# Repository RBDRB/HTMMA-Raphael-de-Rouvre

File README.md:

# HTMMA-Raphael-de-Rouvre
## Traqueur GPS Hors-ligne
Le PCB est destiné à construire un GPS de randonnée hors ligne.
L'objectif n'est pas de reproduire une smartwatch ou un GPS de navigation complet, mais de faire un petit appareil simple et autonome (sauf affichage externe en wifi sur l'ESP) pour l'exécution d'une trace GPX et le suivi d'une trace GPX.

### Choix des composants 

- Calculateur : Pour faire fonctionner les composants entre eux, traiter le GPX et l'interface graphique, et la transmettre en wifi
-> XIAO ESP 32 S3 : Celui à disposition, mais qui s'est avéré parfait pour le projet avec sa taille réduite et ses nombreux GPIO
  
- GPS : Pour récuperer la position en temps réel de l'appareil
-> ATGM336H : Module GNSS peu coûteux, compact, faible consommation par rapport à de nombreuses solutions GNSS plus complexes, sortie UART simple
  
- Mesure d'altitude
-> BMP280 : Très petit, très faible consommation et interface I²C/SPI simple

- Contrôles : Pour naviguer sans écran tactile
-> EC11

- Buzzer : Pour les alertes

- Stockage : Pour conserver les GPX
-> Port à carte Micro-SD

- Condensateurs : Stabiliser 

### Disposition 

Port USB-C de l'ESP 32 et port Micro SD accessibles 

### Rendu 3D : 

Affichage et Alimentation à part

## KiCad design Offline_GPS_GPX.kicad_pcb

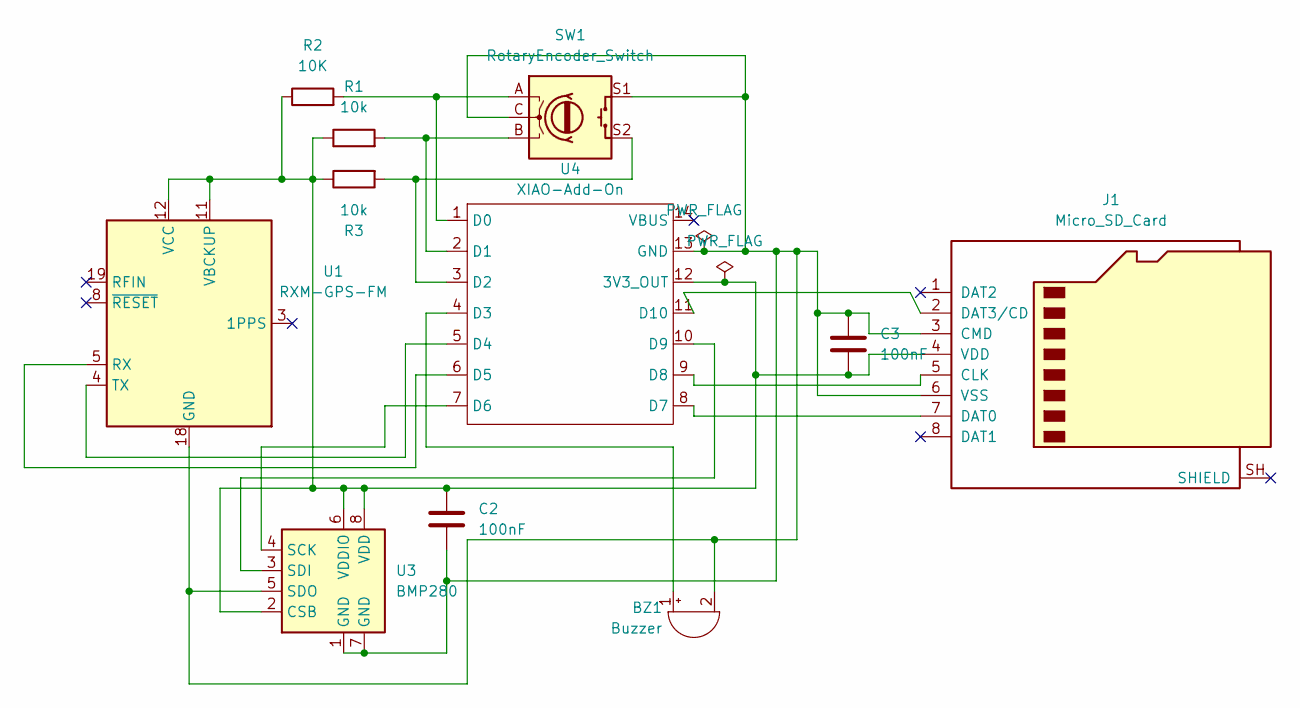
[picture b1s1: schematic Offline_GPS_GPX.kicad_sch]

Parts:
BZ1: Buzzer; WDFN-10-1EP_3x3mm_P0.5mm_EP1.8x2.5mm
C2, C3: 100nF; Balun_Johanson_0900PC15J0013
J1: Micro_SD_Card; microSD_HC_Molex_47219-2001
R1, R3: 10k; TO-92_Inline
R2: 10K; TO-92_Inline
SW1: RotaryEncoder_Switch; RotaryEncoder_Bourns_Horizontal_PEC09-2xxxF-Sxxxx
U1: RXM-GPS-FM; Linx_RXM-GPS
U3: BMP280; Bosch_LGA-8_2x2.5mm_P0.65mm_ClockwisePinNumbering
U4: XIAO-Add-On; XIAO-14P-Add-On

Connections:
unnamed: BZ1.1 (+), U4.4 (D3)
unnamed: BZ1.2 (-), C2.2, C3.2, J1.3 (CMD), J1.6 (VSS), SW1.C, SW1.S1, U1.18 (GND), U1.20 (GND), U1.21 (GND), U1.22 (GND), U3.1 (GND), U3.5 (SDO), U3.7 (GND), U4.13 (GND)
unnamed: J1.5 (CLK), U4.9 (D8)
unnamed: J1.7 (DAT0), U4.8 (D7)
unnamed: J1.2 (DAT3/CD), U4.11 (D10)
unnamed: C2.1, C3.1, J1.4 (VDD), R1.1, R2.1, R3.1, U1.11 (VBCKUP), U1.12 (VCC), U3.2 (CSB), U3.6 (VDDIO), U3.8 (VDD), U4.12 (3V3_OUT)
unnamed: U1.5 (RX), U4.6 (D5)
unnamed: U1.4 (TX), U4.5 (D4)
unnamed: U3.4 (SCK), U4.7 (D6)
unnamed: U3.3 (SDI), U4.10 (D9)
unnamed: R2.2, SW1.A, U4.1 (D0)
unnamed: R1.2, SW1.B, U4.2 (D1)
unnamed: R3.2, SW1.S2, U4.3 (D2)

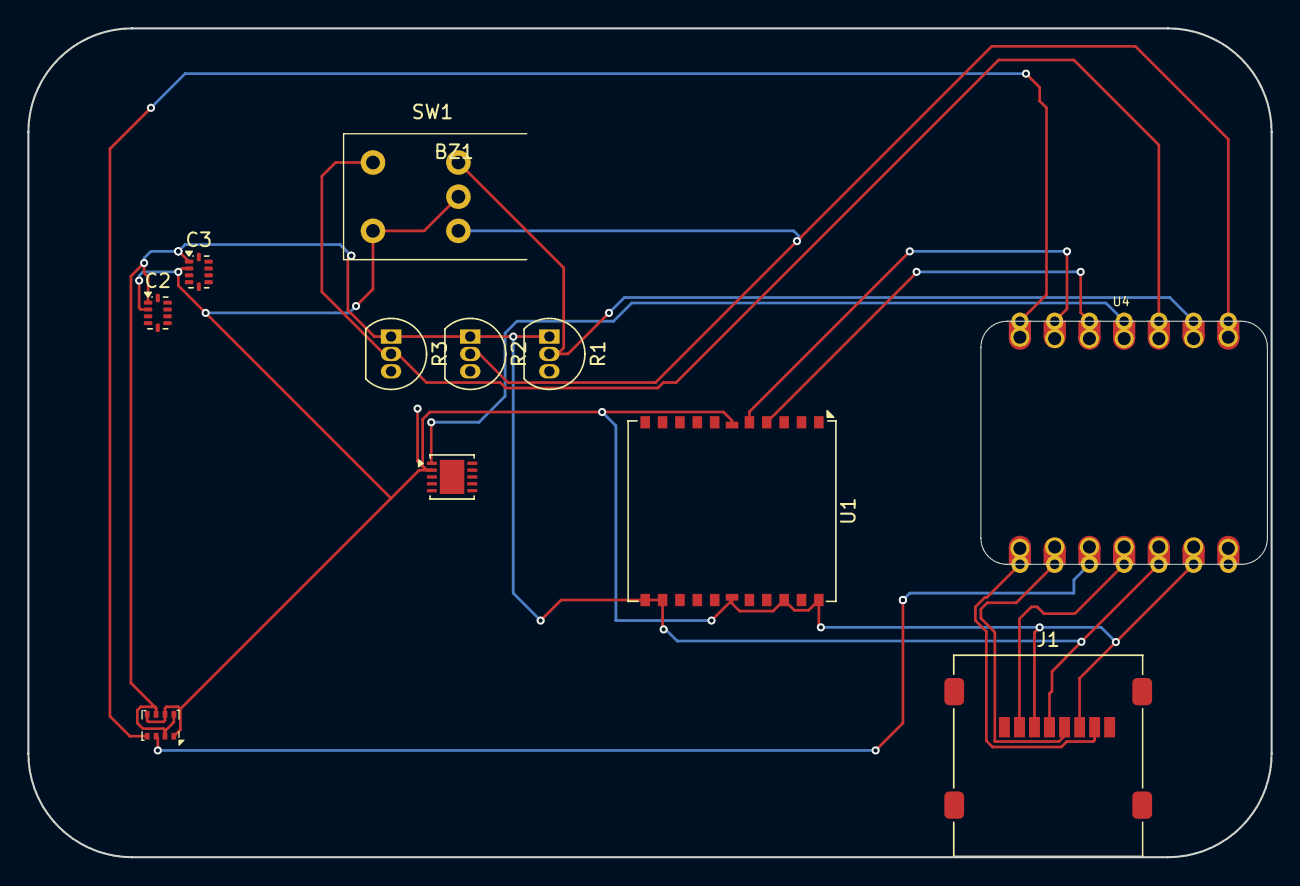
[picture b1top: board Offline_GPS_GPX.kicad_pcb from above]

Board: 2 copper layers, 90.9 x 60.6 mm, 11 parts (0 on the bottom side), 13 nets.

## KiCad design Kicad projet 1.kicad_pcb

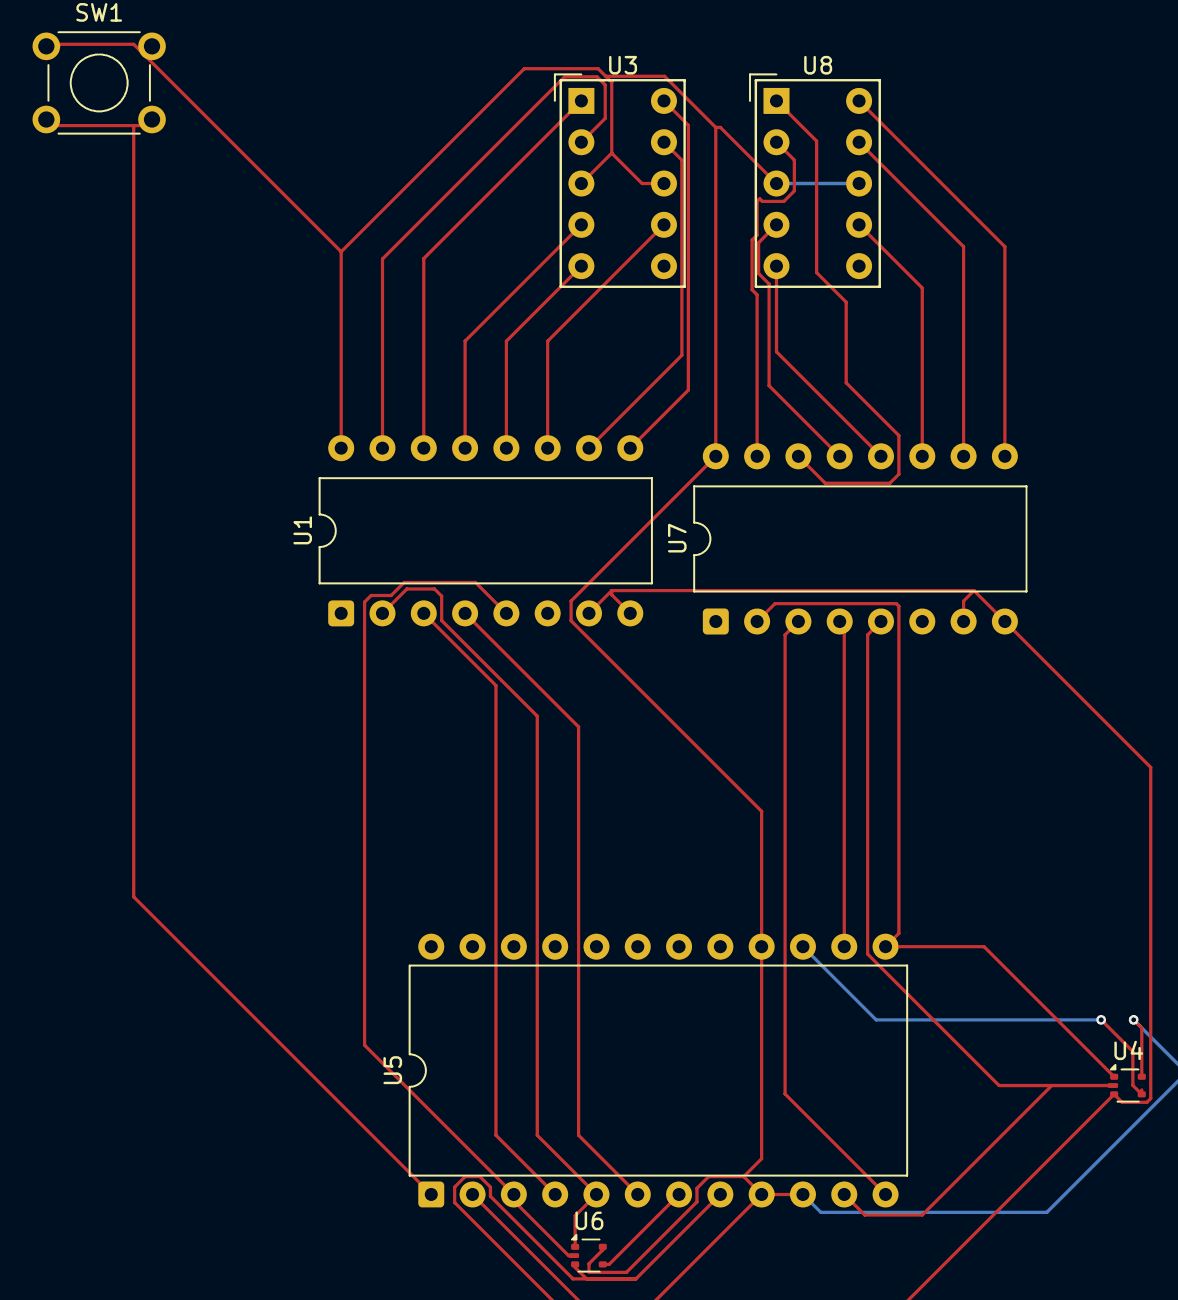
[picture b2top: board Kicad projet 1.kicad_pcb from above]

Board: 2 copper layers, 8 parts (0 on the bottom side), 27 nets.

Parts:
SW1: SW_Push; SW_TH_Tactile_Omron_B3F-107x
U1, U7: 4056; DIP-16_W10.16mm
U3, U8: SA39-11EWA; HDSP-A151
U4, U6: 74AHC1G08; SOT-665
U5: 4518; DIP-24_W15.24mm

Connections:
+5V: SW1.1, U1.16 (VDD), U3.3 (CA), U3.8 (CA), U4.5 (VCC), U5.2 (Enable), U5.9 (CK), U5.10 (Enable), U5.16 (VDD), U6.5 (VCC), U7.16 (VDD), U8.3 (CA), U8.8 (CA)
GND: U1.7 (VEE), U1.8 (VSS), U4.3 (GND), U5.8 (VSS), U6.3 (GND), U7.7 (VEE), U7.8 (VSS)
unnamed: U1.5 (2^0), U5.3 (Q1), U6.2
unnamed: U1.3 (2^1), U5.4 (Q2)
unnamed: U1.2 (2^2), U5.5 (Q3), U6.1
unnamed: U1.4 (2^3), U5.6 (Q4)
unnamed: U1.9 (a), U3.10 (A)
unnamed: U1.10 (b), U3.9 (B)
unnamed: U1.11 (c), U3.7 (C)
unnamed: U1.12 (d), U3.5 (D)
unnamed: U1.13 (e), U3.4 (E)
unnamed: U1.15 (f), U3.2 (F)
unnamed: U1.14 (g), U3.1 (G)
unnamed: SW1.2, U5.1 (CK)
unnamed: U5.7 (Reset), U6.4
unnamed: U4.2, U5.11 (Q1), U7.5 (2^0)
unnamed: U5.12 (Q2), U7.3 (2^1)
unnamed: U4.1, U5.13 (Q3), U7.2 (2^2)
unnamed: U5.14 (Q4), U7.4 (2^3)
unnamed: U4.4, U5.15 (Reset)
unnamed: U7.9 (a), U8.10 (A)
unnamed: U7.10 (b), U8.9 (B)
unnamed: U7.11 (c), U8.7 (C)
unnamed: U7.12 (d), U8.5 (D)
unnamed: U7.13 (e), U8.4 (E)
unnamed: U7.15 (f), U8.2 (F)
unnamed: U7.14 (g), U8.1 (G)
